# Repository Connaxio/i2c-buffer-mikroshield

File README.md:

# I2C Buffer mikroShield

This mikroBUS-compatible mikroShield protects a mainboard's power and I2C lines when connecting unpowered off-board devices. For self-powered devices, an isolated adapter board is preferred.

## Features

- PTC resettable fuse on the 5 V supply rail (200 mA hold, 400 mA trip)
- Dedicated 3.3 V linear regulator from the protected 5 V rail
- I2C buffer / repeater (5500 V HBM ESD)
- ESD protection (TVS) diodes on external SCL, SDA, and 3.3V supply lines
- Series current-limiting resistors on the SCL and SDA external signal lines
- 100 mils output connector compatible with Grove, quiic, and STEMMA adapter boards for a direct board-to-board connection.

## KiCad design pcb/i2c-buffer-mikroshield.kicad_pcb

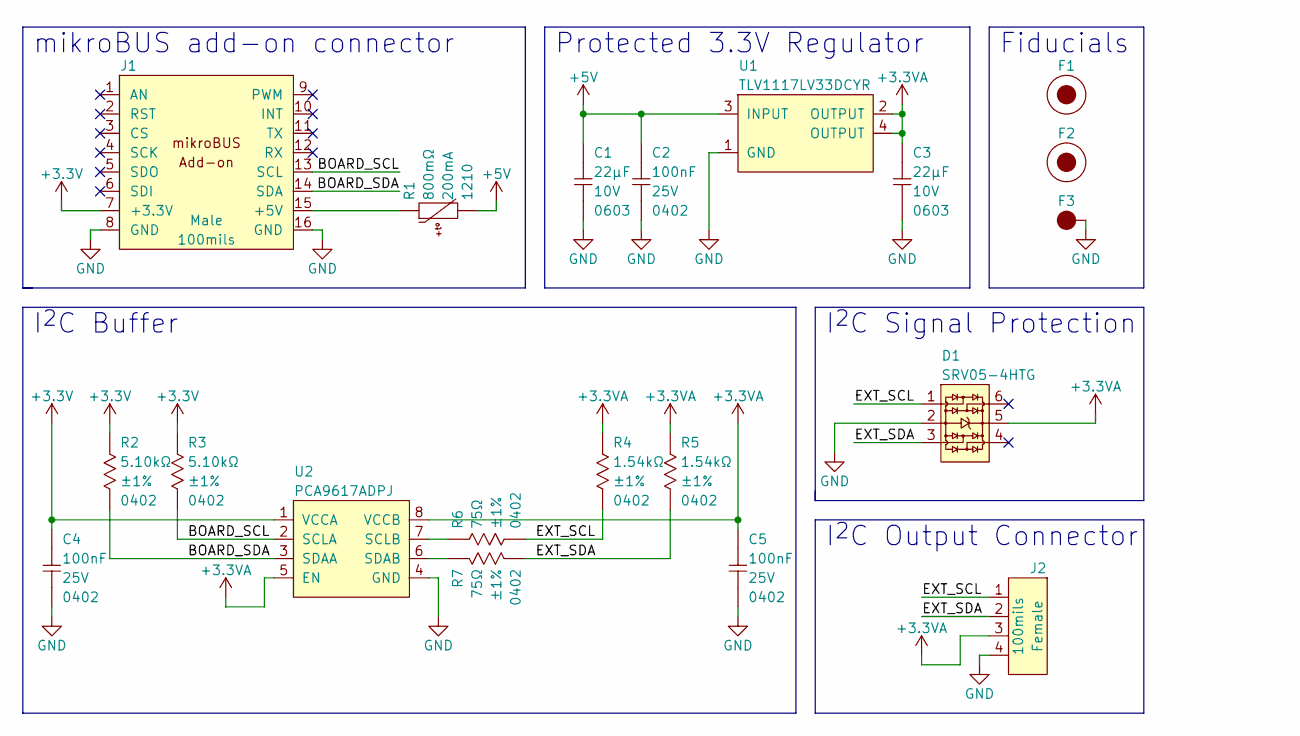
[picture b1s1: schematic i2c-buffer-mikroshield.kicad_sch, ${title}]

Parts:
C1, C3: CAP_CER_22UF_10V_0603; CAP_CER_0603_1608M; Tolerance ±20%; Voltage 10V; Manufacturer Part Number CL10A226MP8NUNE
C2, C4, C5: CAP_CER_100NF_25V_0402; CAP_CER_0402_1005M; Tolerance ±10%; Voltage 25V; Manufacturer Part Number CL05A104KA5NNNC
D1: DIO_TVS_SRV05-4HTG; SOT-23-6; Voltage 6V; Manufacturer Part Number SRV05-4HTG
F1, F2: FID_1X3
F3: FID_1X1
J1: CON_HDR_MIKROBUS_ADDON_TH; Voltage 350V
J2: CON_HDR_100MILS_F_TH_RA_1X4; Voltage 350V
R1: PTC_SMD1210B010TF; RES_1210_3225M; Tolerance 400mA; Voltage 30V; Manufacturer Part Number SMD1210B010TF
R2, R3: RES_5.10KΩ_1%_0402; RES_0402_1005M; Tolerance ±1%; Voltage 50V; Manufacturer Part Number RMCF0402FT5K10
R4, R5: RES_1.54KΩ_1%_0402; RES_0402_1005M; Tolerance ±1%; Voltage 50V; Manufacturer Part Number RMCF0402FT1K54
R6, R7: RES_75Ω_1%_0402; RES_0402_1005M; Tolerance ±1%; Voltage 50V; Manufacturer Part Number RMCF0402FT75R0
U1: REG_LDO_TLV1117LV33DCYR; SOT-223-4; Voltage 5.5V; Manufacturer Part Number TLV1117LV33DCYR
U2: BUF_I2C_PCA9617ADPJ; TSSOP-8_3X3_P0.65; Voltage 2.7V to 5.5V; Manufacturer Part Number PCA9617ADPJ

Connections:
+3.3V: C4.1, J1.7 (+3.3V), R2.1, R3.1, U2.1 (VCCA)
+3.3VA: C3.1, C5.1, D1.5, J2.3, R4.1, R5.1, U1.2 (OUTPUT), U1.4 (OUTPUT), U2.5 (EN), U2.8 (VCCB)
+5V: C1.1, C2.1, R1.2, U1.3 (INPUT)
/BOARD_SCL: J1.13 (SCL), R3.2, U2.2 (SCLA)
/BOARD_SDA: J1.14 (SDA), R2.2, U2.3 (SDAA)
/EXT_SCL: D1.1, J2.1, R4.2, R6.2
/EXT_SDA: D1.3, J2.2, R5.2, R7.2
GND: C1.2, C2.2, C3.2, C4.2, C5.2, D1.2, F3.1, J1.8 (GND), J1.16 (GND), J2.4, U1.1 (GND), U2.4 (GND)
unnamed: J1.15 (+5V), R1.1
unnamed: R7.1, U2.6 (SDAB)
unnamed: R6.1, U2.7 (SCLB)

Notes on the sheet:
I^{2}C Buffer
I^{2}C Signal Protection
Fiducials
I^{2}C Output Connector
Protected 3.3V Regulator
mikroBUS add-on connector

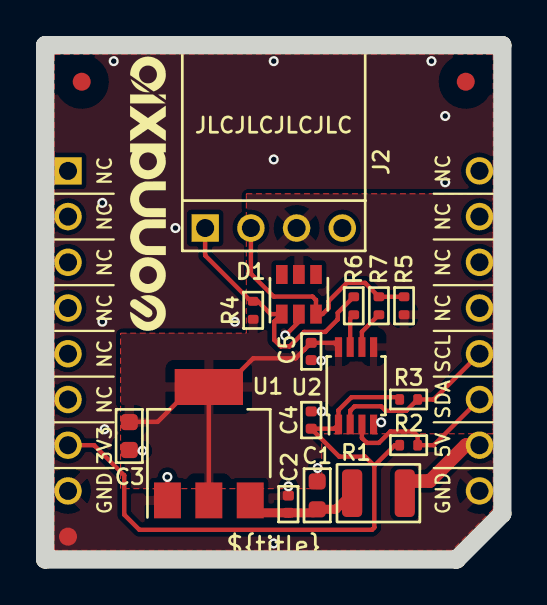
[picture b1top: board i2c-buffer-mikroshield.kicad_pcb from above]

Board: 2 copper layers, 25.4 x 28.6 mm, 20 parts (0 on the bottom side), 11 nets.

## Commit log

2023-01-23 First version, DRC pass
2023-01-23 Remove save file

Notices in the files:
pcb/i2c-buffer-mikroshield.kicad_pcb:
Licensed under
CERN-OHL-W v2
